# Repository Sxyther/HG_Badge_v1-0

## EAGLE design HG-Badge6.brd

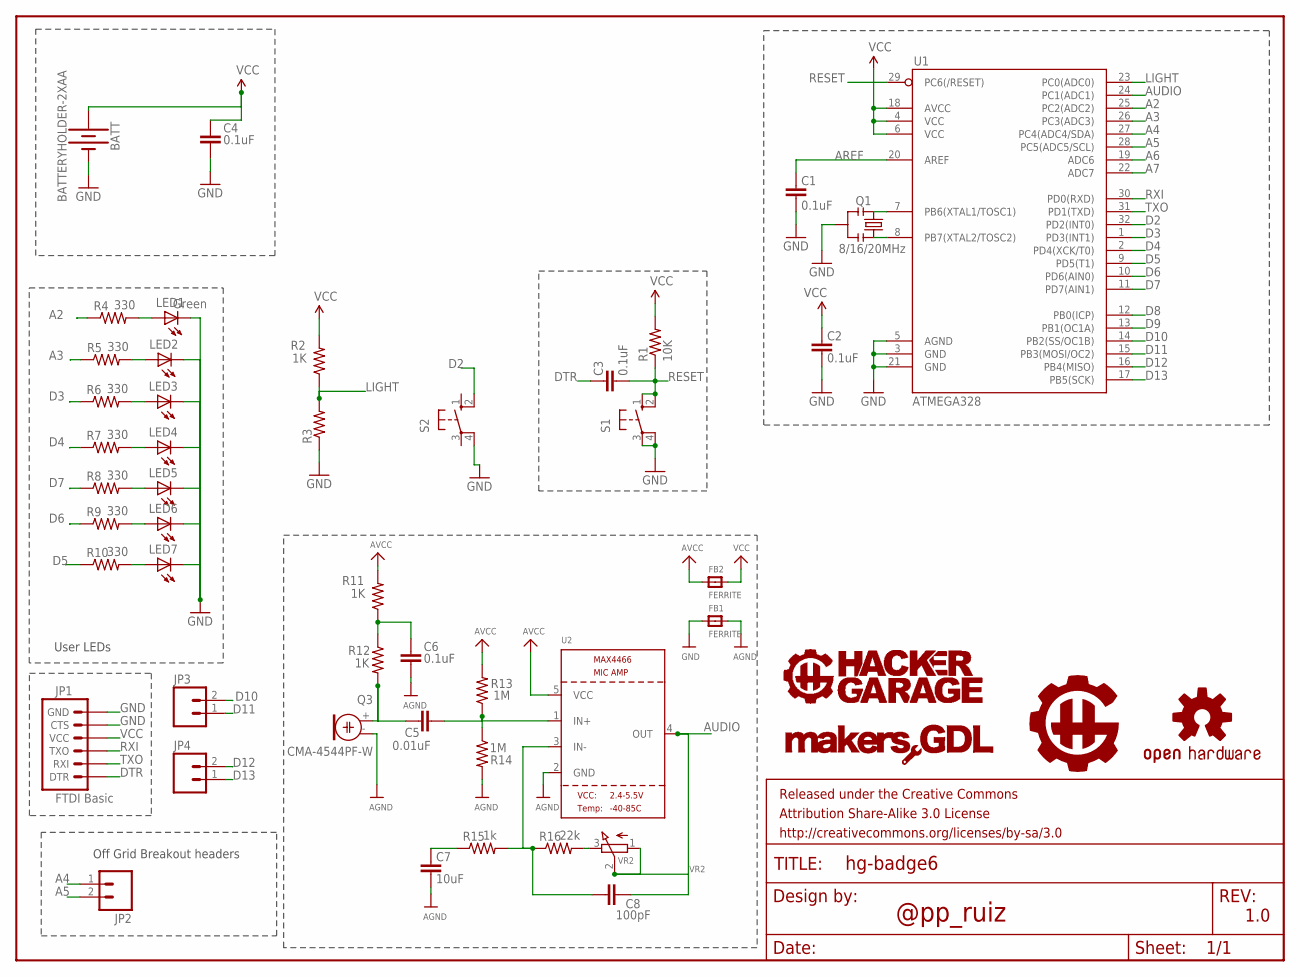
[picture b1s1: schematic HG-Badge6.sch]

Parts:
BATT: BATTERYHOLDER-2XAA; BATT-HOLDER-2XAAA
C1, C2, C3, C4, C6: 0.1uF; 0603-CAP
C5: 0.01uF; 0603-CAP
C7: 10uF; 0603-CAP
C8: 100pF; 0603-CAP
FB1, FB2: FERRITE; 0805
FRAME1: FRAME-LETTER; CREATIVE_COMMONS
JP1: FTDI Basic; 1X06
JP2, JP3, JP4: M02PTH; 1X02
LED1, LED2, LED3, LED4, LED5, LED6, LED7: Green; 0603-LED-ALT1
Q1: 8/16/20MHz; RESONATOR-SMD-1:1
Q3: CMA-4544PF-W; ELECTRET_9.7
R1: 10K; 0603-RES
R2, R11, R12: 1K; 0603-RES
R3: R-US_0204/2V; 0204V
R4, R5, R6, R7, R8, R9, R10: 330; 0603-RES
R13, R14: 1M; 0603-RES
R15: 1k; 0603-RES
R16: 22k; 0603-RES
S1, S2: 10-XX; B3F-10XX
U1: ATMEGA328; TQFP32-08
U2: MAX4466EXK+T; SC70-5
U$1: HG-BADGE-FULL; HG-BADGE
U$3: OSHW-LOGOS; OSHW-LOGO-S
U$4: MAKERSGDLLOGO-SMALL; MAKERSGGL-SMALL
U$5: HACKERGARAGEFULL; HACKERGARAGEFULL-SMALL
VR2: VR2; TRIMPOT_BOURNS_TC33X-2

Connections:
A2: R4.1, U1.25 (PC2(ADC2))
A3: R5.1, U1.26 (PC3(ADC3))
A4: JP2.1, U1.27 (PC4(ADC4/SDA))
A5: JP2.2, U1.28 (PC5(ADC5/SCL))
A6: U1.19 (ADC6)
A7: U1.22 (ADC7)
AGND: C6.1, C7.1, FB1.2, Q3.- (1), R14.2, U2.2 (GND)
AREF: C1.2, U1.20 (AREF)
AUDIO: C8.1, U1.24 (PC1(ADC1)), U2.4 (OUT), VR2.1 (A), VR2.2 (S)
AVCC: FB2.1, R11.2, R13.2, U2.5 (VCC)
D2: S2.2 (S1), U1.32 (PD2(INT0))
D3: R6.1, U1.1 (PD3(INT1))
D4: R7.1, U1.2 (PD4(XCK/T0))
D5: R10.1, U1.9 (PD5(T1))
D6: R9.1, U1.10 (PD6(AIN0))
D7: R8.1, U1.11 (PD7(AIN1))
D8: U1.12 (PB0(ICP))
D9: U1.13 (PB1(OC1A))
D10: JP3.2, U1.14 (PB2(SS/OC1B))
D11: JP3.1, U1.15 (PB3(MOSI/OC2))
D12: JP4.2, U1.16 (PB4(MISO))
D13: JP4.1, U1.17 (PB5(SCK))
DTR: C3.2, JP1.1 (DTR)
GND: BATT.P$1 (-), C1.1, C2.1, C4.1, FB1.1, JP1.5 (CTS), JP1.6 (GND), LED1.C, LED2.C, LED3.C, LED4.C, LED5.C, LED6.C, LED7.C, Q1.2, R3.1, S1.3, S1.4 (P1), S2.4 (P1), U1.3 (GND), U1.5 (AGND), U1.21 (GND)
LIGHT: R2.1, R3.2, U1.23 (PC0(ADC0))
unnamed: Q1.3, U1.8 (PB7(XTAL2/TOSC2))
unnamed: Q1.1, U1.7 (PB6(XTAL1/TOSC1))
unnamed: LED4.A, R7.2
unnamed: LED5.A, R8.2
unnamed: LED6.A, R9.2
unnamed: LED7.A, R10.2
unnamed: LED3.A, R6.2
unnamed: LED2.A, R5.2
unnamed: LED1.A, R4.2
unnamed: C8.2, R15.2, R16.1, U2.3 (IN-)
unnamed: C5.2, Q3.+ (2), R12.2
unnamed: C6.2, R11.1, R12.1
unnamed: C5.1, R13.1, R14.1, U2.1 (IN+)
unnamed: R16.2, VR2.3 (E)
unnamed: C7.2, R15.1
RESET: C3.1, R1.1, S1.1 (S), S1.2 (S1), U1.29 (PC6(/RESET))
RXI: JP1.3 (TXO), U1.30 (PD0(RXD))
TXO: JP1.2 (RXI), U1.31 (PD1(TXD))
VCC: BATT.P$2 (+), C2.2, C4.2, FB2.2, JP1.4 (VCC), R1.2, R2.2, U1.4 (VCC), U1.6 (VCC), U1.18 (AVCC)

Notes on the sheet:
Off Grid Breakout headers
User LEDs
1.0
@pp_ruiz

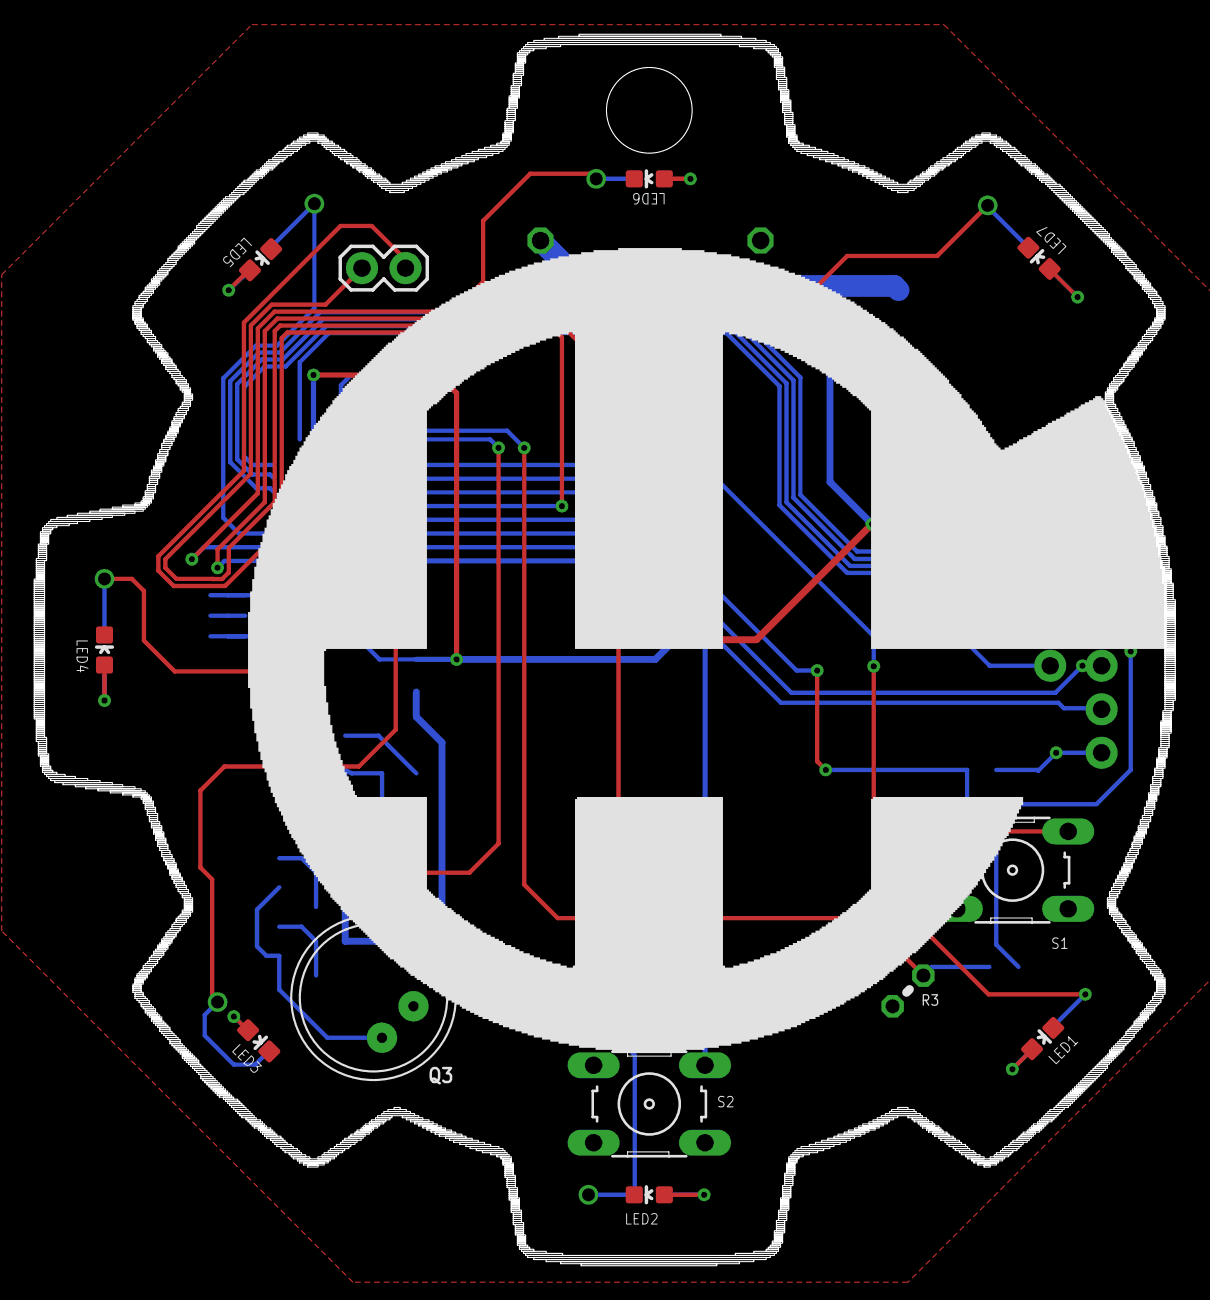
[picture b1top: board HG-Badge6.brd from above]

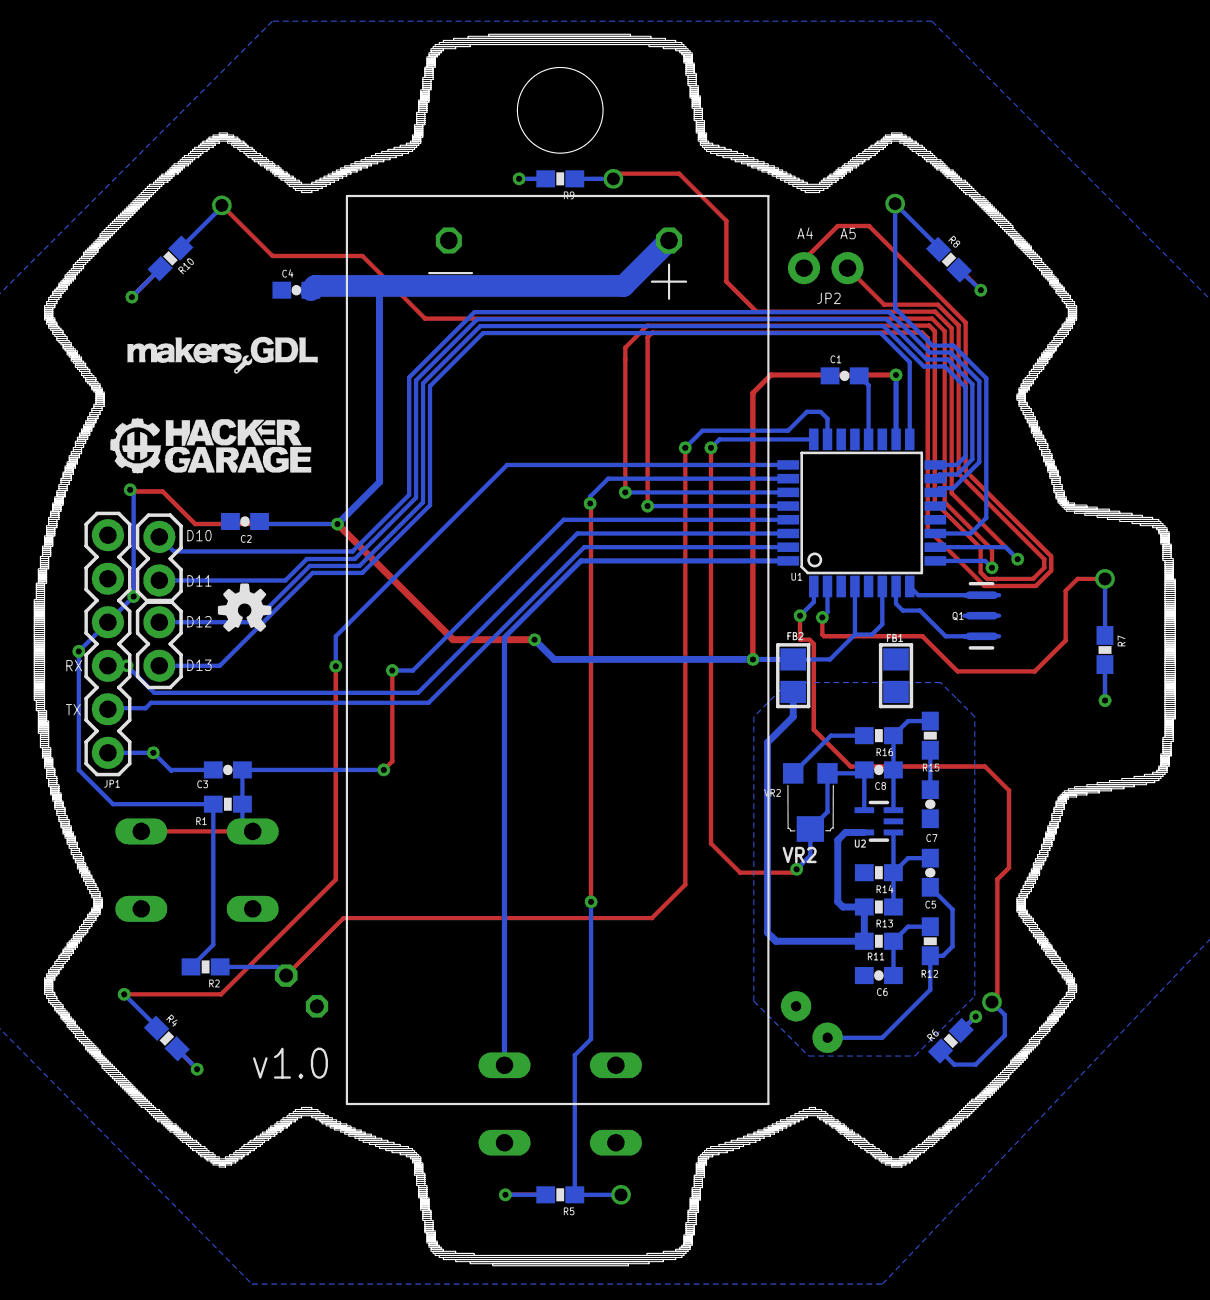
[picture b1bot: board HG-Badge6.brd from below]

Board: 2 copper layers, 66.6 x 71.9 mm, 50 parts (36 on the bottom side), 40 nets.

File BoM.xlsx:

Part | Value | Device | Package | Description
C1 | 0.1uF | Capacitor | 0603-CAP | Capacitor | Any 0603 capacitor
C2 | 0.1uF | Capacitor | 0603-CAP | Capacitor | Any 0603 capacitor
C3 | 0.1uF | Capacitor | 0603-CAP | Capacitor | Any 0603 capacitor
C4 | 10uF | Capacitor | 1206-CAP | Capacitor Polarized | Any 1206 capacitor
C5 | 0.01uF | Capacitor | 0603-CAP | Capacitor | Any 1206 capacitor
C6 | 0.1uF | Capacitor | 0603-CAP | Capacitor | Any 0603 capacitor
C7 | 10uF | Capacitor | 0603-CAP | Capacitor | Any 0603 capacitor
C8 | 100pF | Capacitor | 0603-CAP | Capacitor | Any 0603 capacitor
FB1 | 300 ohm | FERRITE0805 | 0805-Ferrite | Ferrite Bead | https://www.digikey.com/product-detail/en/bourns-inc/MU2029-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
FB2 | 300 ohm | FERRITE0805 | 0805-Ferrite | Ferrite Bead | https://www.digikey.com/product-detail/en/bourns-inc/MU2029-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
LED1 | White | LED | 0603-LED | LEDs | https://www.digikey.com/product-detail/en/osram-opto-semicon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
LED2 | White | LED | 0603-LED | LEDs | https://www.digikey.com/product-detail/en/osram-opto-semicon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
LED3 | White | LED | 0603-LED | LEDs | https://www.digikey.com/product-detail/en/osram-opto-semicon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
LED4 | White | LED | 0603-LED | LEDs | https://www.digikey.com/product-detail/en/osram-opto-semicon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
LED5 | White | LED | 0603-LED | LEDs | https://www.digikey.com/product-detail/en/osram-opto-semicon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
LED6 | White | LED | 0603-LED | LEDs | https://www.digikey.com/product-detail/en/osram-opto-semicon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
LED7 | White | LED | 0603-LED | LEDs | https://www.digikey.com/product-detail/en/osram-opto-semicon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
Q1 | 8/16/20MHz | RESONATOR1:1 | RESONATOR-SMD-1:1 | Resonator | https://www.digikey.com/product-detail/en/murata-electronics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
R1 | 10K | RESISTOR0603-RES | 0603-RES | Resistor | Any 0603 resistor
R2 | 1K | RESISTOR0603-RES | 0603-RES | Resistor | Any 0603 resistor
R4 | 330 | RESISTOR0603-RES | 0603-RES | Resistor | Any 0603 resistor
R5 | 330 | RESISTOR0603-RES | 0603-RES | Resistor | Any 0603 resistor
R6 | 330 | RESISTOR0603-RES | 0603-RES | Resistor | Any 0603 resistor
R7 | 330 | RESISTOR0603-RES | 0603-RES | Resistor | Any 0603 resistor
R8 | 330 | RESISTOR0603-RES | 0603-RES | Resistor | Any 0603 resistor
R9 | 330 | RESISTOR0603-RES | 0603-RES | Resistor | Any 0603 resistor
R10 | 330 | RESISTOR0603-RES | 0603-RES | Resistor | Any 0603 resistor
R11 | 1K | RESISTOR0603-RES | 0603-RES | Resistor | Any 0603 resistor
R12 | 1K | RESISTOR0603-RES | 0603-RES | Resistor | Any 0603 resistor
R13 | 1M | RESISTOR0603-RES | 0603-RES | Resistor | Any 0603 resistor
R14 | 1M | RESISTOR0603-RES | 0603-RES | Resistor | Any 0603 resistor
R15 | 1k | RESISTOR0603-RES | 0603-RES | Resistor | Any 0603 resistor
R16 | 22k | RESISTOR0603-RES | 0603-RES | Resistor | Any 0603 resistor
U1 | ATMEGA328 | ATMEGA168 | TQFP32-08 |  | https://www.digikey.com/product-detail/en/microchip-technolo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
U2 | MAX4466EXK+T | MAX4466"" | SC70-5 | MAX4466 - Microphone Pre-Amp | https://www.digikey.com/product-detail/en/maxim-integrated/M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

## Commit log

2018-12-18 gen6 airwaves fixed

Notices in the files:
parts and their libraries:
microbuilder: This work is placed in the public domain, and may be freely used for commercial and non-commercial work with the following conditions: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
SparkFun-Aesthetics: Licensing: CC v3.0 Share-Alike You are welcome to use this library for commercial purposes.
